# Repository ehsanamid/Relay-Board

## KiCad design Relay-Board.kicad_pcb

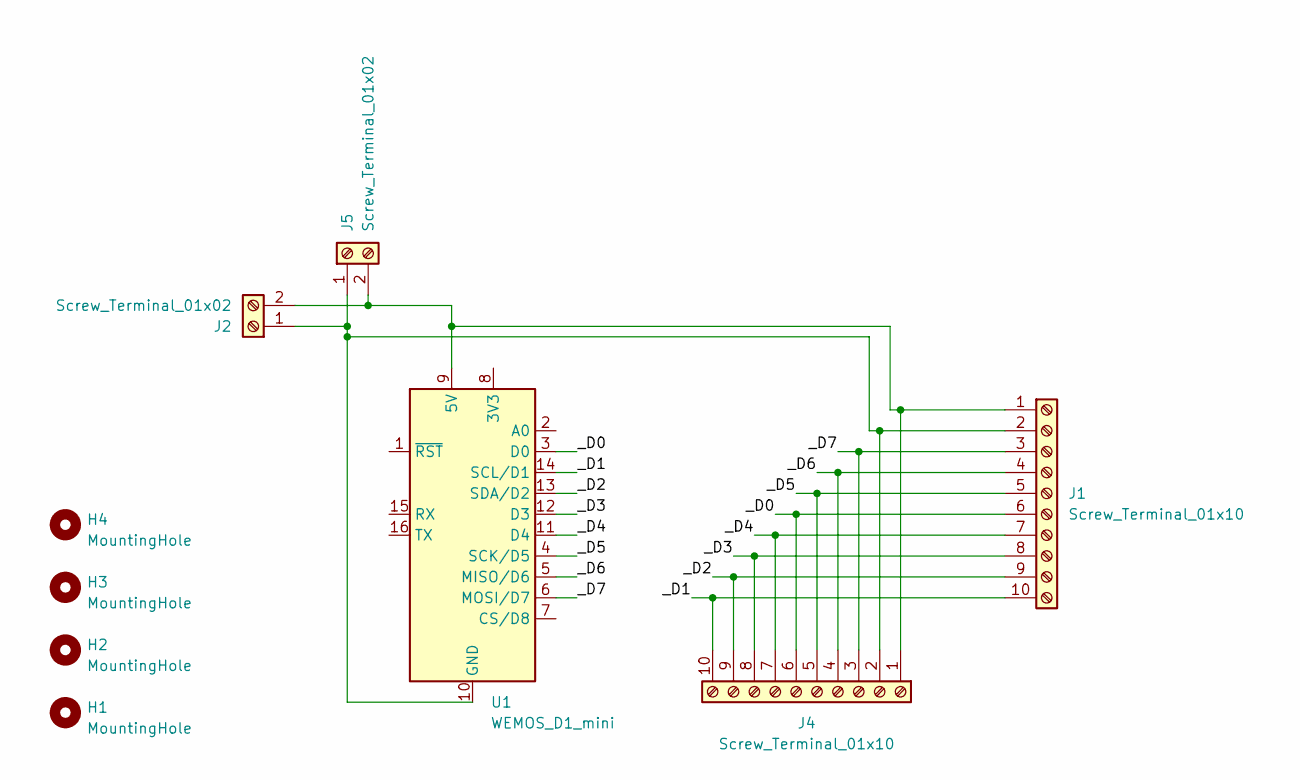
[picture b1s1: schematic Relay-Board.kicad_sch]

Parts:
H1, H2, H3, H4: MountingHole; MountingHole_3.2mm_M3
J1: Screw_Terminal_01x10; TerminalBlock_Xinya_XY308-2.54-10P_1x10_P2.54mm_Horizontal
J2: Screw_Terminal_01x02; TerminalBlock_CUI_TB007-508-02_1x02_P5.08mm_Horizontal
J4: Screw_Terminal_01x10; TerminalBlock_CUI_TB007-508-10_1x10_P5.08mm_Horizontal
J5: Screw_Terminal_01x02; TerminalBlock_Xinya_XY308-2.54-2P_1x02_P2.54mm_Horizontal
U1: WEMOS_D1_mini; WEMOS_D1_mini_light

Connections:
/_D0: J1.6, J4.6, U1.3 (D0)
/_D1: J1.10, J4.10, U1.14 (SCL/D1)
/_D2: J1.9, J4.9, U1.13 (SDA/D2)
/_D3: J1.8, J4.8, U1.12 (D3)
/_D4: J1.7, J4.7, U1.11 (D4)
/_D5: J1.5, J4.5, U1.4 (SCK/D5)
/_D6: J1.4, J4.4, U1.5 (MISO/D6)
/_D7: J1.3, J4.3, U1.6 (MOSI/D7)
unnamed: J1.1, J2.2, J4.1, J5.2, U1.9 (5V)
unnamed: J1.2, J2.1, J4.2, J5.1, U1.10 (GND)

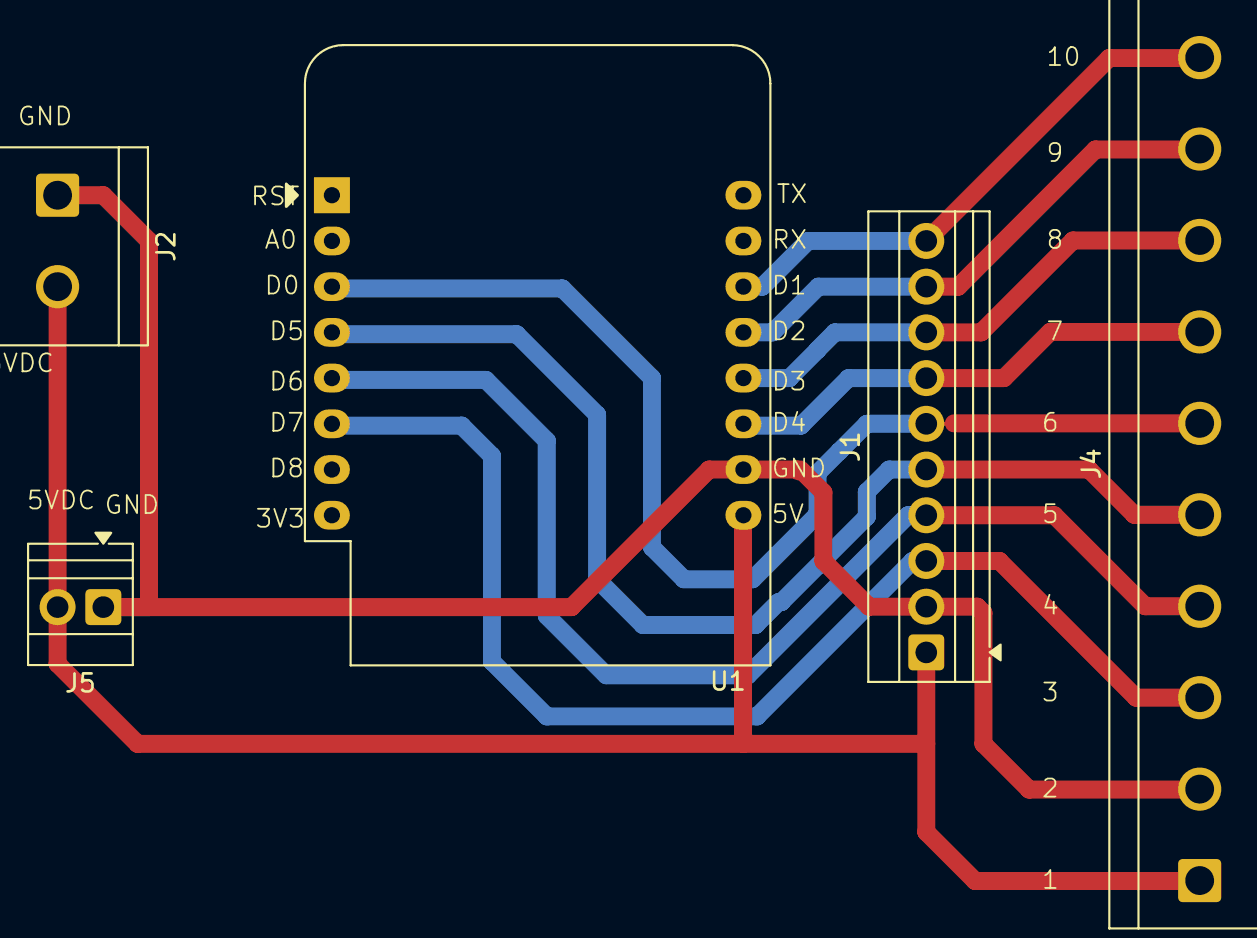
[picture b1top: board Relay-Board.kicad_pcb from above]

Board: 2 copper layers, 9 parts (0 on the bottom side), 10 nets.

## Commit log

2026-01-29 init
2026-01-29 2026-01-29
2026-01-30 2026-01-30
